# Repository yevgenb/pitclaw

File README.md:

#  Pit Claw

BBQ temperature monitor and controller built around the WT32-SC01 Plus: an
ESP32-S3 with a 3.5-inch, 480×320 landscape capacitive touchscreen. Pit Claw reads
one pit probe and two meat probes, controls a blower and optional servo damper,
and provides a web dashboard for monitoring and control. The touchscreen and
temperature control work without Wi-Fi.

## Current project state

As of **9 September 2026**:

| Area | State |
| --- | --- |
| Firmware | Version **0.2.0**, built and flashed to a WT32-SC01 Plus; upload verified and the device responded after reboot. |
| Touchscreen | LVGL Home, Graph, Settings, temperature editors, shared alarms, and first-boot setup are implemented. The latest polish is included in the flashed build. |
| Web interface | Live temperatures, history and prediction graphs, session controls/export, settings, and manual firmware OTA. Supports deployment under an Nginx path prefix. |
| Carrier PCB | **Rev B-T2F0-A5807-S4** routed prototype. Recorded KiCad ERC, DRC, schematic parity, and unconnected-item checks pass. A reviewed bare-board fabrication package is available; physical qualification remains. |
| Enclosure | **r7 landscape fit prototype**, with exported STLs, fit coupons, and a print guide. Physical module and printed-part fit still need verification. |

The firmware and simulator builds, **132 native test cases**, and the headless
LVGL checks passed on 8 September 2026. The LVGL checks include 123 navigation
taps and editor, unit, alarm, probe-state, and layout transitions. This validation
does not establish smoker temperature accuracy or qualify the new carrier's
electrical loads, thermal behavior, or physical fit.

## Touchscreen

The current dashboard uses large temperature readings, rounded cards and
navigation buttons, neutral status labels, and consistent edit icons. Smaller
degree symbols follow changing values and disappear for disconnected probes.
The image above is a native 480×320 LVGL render with example readings.

- Tap the pit card to change its setpoint, or a meat card to edit that probe's
  target. Tap for one-degree steps or hold for five-degree steps; Cancel discards
  the draft value.
- Switch between Fahrenheit and Celsius without changing the stored control
  targets. Graph history uses elapsed sample time and a dashed setpoint line.
- Alarm controls remain available on Home, Graph, Settings, and above an open
  editor. Disconnected probes display dashes.
- Setup provides Back navigation, Wi-Fi connection feedback, live probe checks,
  and separate fan, servo, and buzzer test buttons.

## Control and monitoring

- **Three probe inputs:** one pit and two meat channels, using calibrated
  thermistor probes with 2.5 mm jacks. Thermoworks Pro-Series is the intended
  probe family; other probes require suitable coefficients and calibration.
- **PID control:** fan-only, fan-and-damper, and damper-priority modes, with
  startup handling, lid-open detection, and output shutdown on a pit-probe fault.
- **Alarms:** local buzzer, browser audio, and configurable Pushover notifications.
- **Cook sessions:** temperature history, predicted meat completion times, and
  CSV/JSON export. Download a session before starting a new one.
- **Configuration:** persistent settings, probe calibration, and Wi-Fi reconnect.

## Web interface

Open `http://bbq.local` or the controller's LAN IP from a device on the same
network. The dashboard uses WebSocket updates and also works behind an Nginx
directory prefix such as `/newbbq/`; see the
[reverse-proxy guide](firmware/docs/reverse-proxy.md).

PWA installation, service-worker caching, and browser notifications need a secure
context; use HTTPS on the reverse proxy for those features. Live readings still
require a connection to the controller.

Manual firmware updates are available at `/update`. Automatic GitHub release
checks are disabled in the current PlatformIO configuration. `firmware.bin`
includes the web UI, so one firmware upload updates both interfaces while
preserving LittleFS settings and session history.

## Hardware and enclosure

The active design is the
[Rev B-T2F0-A5807-S4 carrier](hardware/carrier-revb/README.md), a 60×92 mm board
with PCB-mounted probe jacks, a blower/servo connector, a 12 V barrel inlet,
an Adafruit 5807 USB-C PD module, and a Traco TSR 2-2450N 5 V / 2 A converter.
A relay selects wall power when present and USB-PD otherwise.

| Resource | Contents |
| --- | --- |
| [Carrier design](hardware/carrier-revb/README.md) | Circuit, power limits, module mounting, and remaining qualification work |
| [Wiring guide](docs/wiring.md) | Current connector pin assignments and assembly wiring |
| [Carrier BOM](hardware/carrier-revb/bom/README.md) | Current parts and recorded pricing |
| [Verification](hardware/carrier-revb/verification/README.md) | Native electrical/layout checks and physical validation limits |
| [JLCPCB prototype package](hardware/carrier-revb/fabrication/jlcpcb-2026-09-06/README.md) | Reviewed Gerber/drill archive for a small bare-board order |
| [Fusion enclosure model](enclosure/fusion-r13/pitclaw-enclosure-r13.f3d) | Editable 104×86×44.9 mm controller case |
| [STL package and print guide](enclosure/fusion-r13/README.md) | Top, bottom, probe fascia, display retainer, USB base, coupons, and assembly guide |

The fabrication documentation records no submitted PCB order. Carrier load,
relay-transfer, thermal, and module-fit checks remain, along with printed
enclosure fit checks. Use the [enclosure guide](enclosure/README.md) for the
current controller case and the separate fan/damper assembly.

## Getting started

### 1. Set up the tools

```sh
git clone https://github.com/yevgenb/pitclaw.git
cd pitclaw
```

Install PlatformIO CLI. Windows users can use the repository's setup script:

```powershell
# Run from an elevated PowerShell in the repository root
powershell -ExecutionPolicy Bypass -File scripts\setup-dev.ps1
```

See [firmware development](docs/firmware-development.md) for prerequisites.
Use the current carrier and wiring guides when assembling hardware.

### 2. Build and flash

Run from `firmware/` with the WT32-SC01 Plus connected over USB:

```sh
cd firmware
pio run -e wt32_sc01_plus
pio run -e wt32_sc01_plus --target upload

```

No filesystem upload is needed for the web UI. A filesystem upload replaces
LittleFS and can erase configuration and session data; normal firmware updates
preserve that filesystem. The display board's programming USB port requires
opening the enclosure; the carrier's external USB-C PD port is for power.

For later manual firmware OTA, open `http://bbq.local/update` and upload
`firmware/.pio/build/wt32_sc01_plus/firmware.bin` from the repository root.

### 3. Complete setup

1. Select °F or °C in the touchscreen wizard.
2. Follow the Wi-Fi QR code and portal instructions, or continue offline with Next.
3. Connect the probes and check their live readings.
4. Tap the fan, servo, and buzzer test buttons and confirm each device operates.
5. Finish setup to enter the dashboard.

Hold a finger on the touchscreen for 10 seconds during the boot splash to request
a factory reset.

## Development and validation

The SDL2 desktop simulator runs the production LVGL screens and serves the web
UI at `http://localhost:3000`. Run these commands from `firmware/`:

```sh
# Native control-logic regression tests
pio test -e native

# Desktop simulator; requires SDL2
pio run -e simulator
.pio/build/simulator/program

# Headless production LVGL interaction checks; run after building the simulator
python3 test/ui/run_checks.py

# Web update and reverse-proxy checks
node test/web/test_release_updates.cjs
node test/web/test_reverse_proxy.cjs
```

On Apple Silicon with Homebrew SDL2, use
`CPATH=/opt/homebrew/include pio run -e simulator` if the headers are not found.
The [display test guide](firmware/test/ui/README.md) explains the capture command
and alternate SDL paths. UI screenshots can be regenerated locally on demand.

| Guide | Topics |
| --- | --- |
| [Firmware development](docs/firmware-development.md) | Build, flash, architecture, and configuration |
| [Display checks](firmware/test/ui/README.md) | Real LVGL pointer events, layout checks, and PNG capture |
| [Web UI development](docs/web-development.md) | Simulator profiles, web assets, and WebSocket protocol |
| [Reverse proxy](firmware/docs/reverse-proxy.md) | Nginx path prefixes, WebSockets, HTTPS, and manual OTA routing |
| [3D printed parts](enclosure/README.md) | Current enclosure, legacy parts, and fan assembly |

## License

TBD

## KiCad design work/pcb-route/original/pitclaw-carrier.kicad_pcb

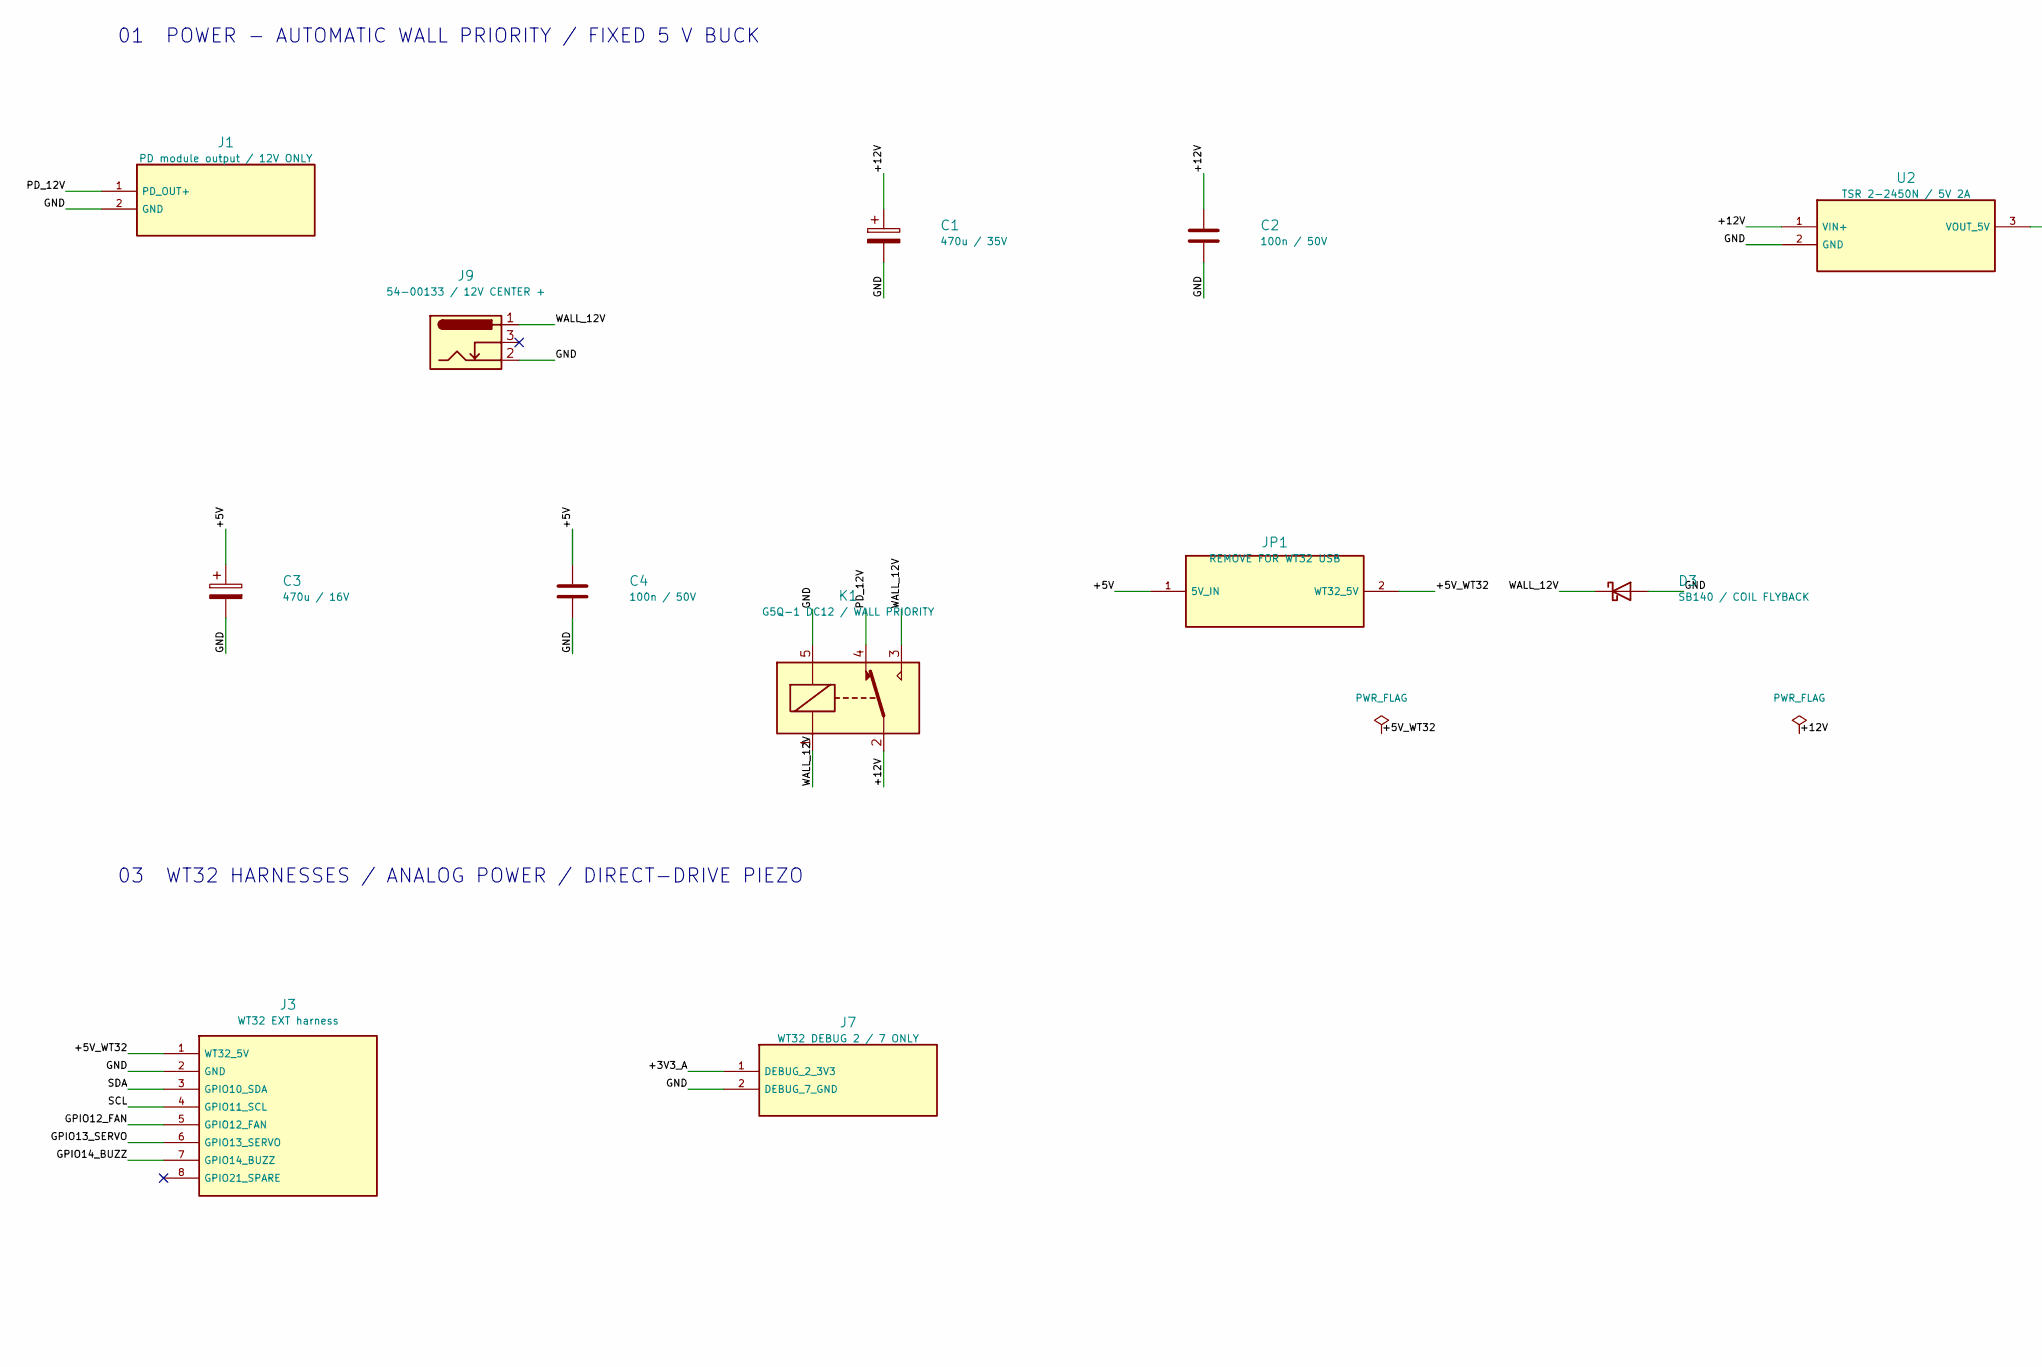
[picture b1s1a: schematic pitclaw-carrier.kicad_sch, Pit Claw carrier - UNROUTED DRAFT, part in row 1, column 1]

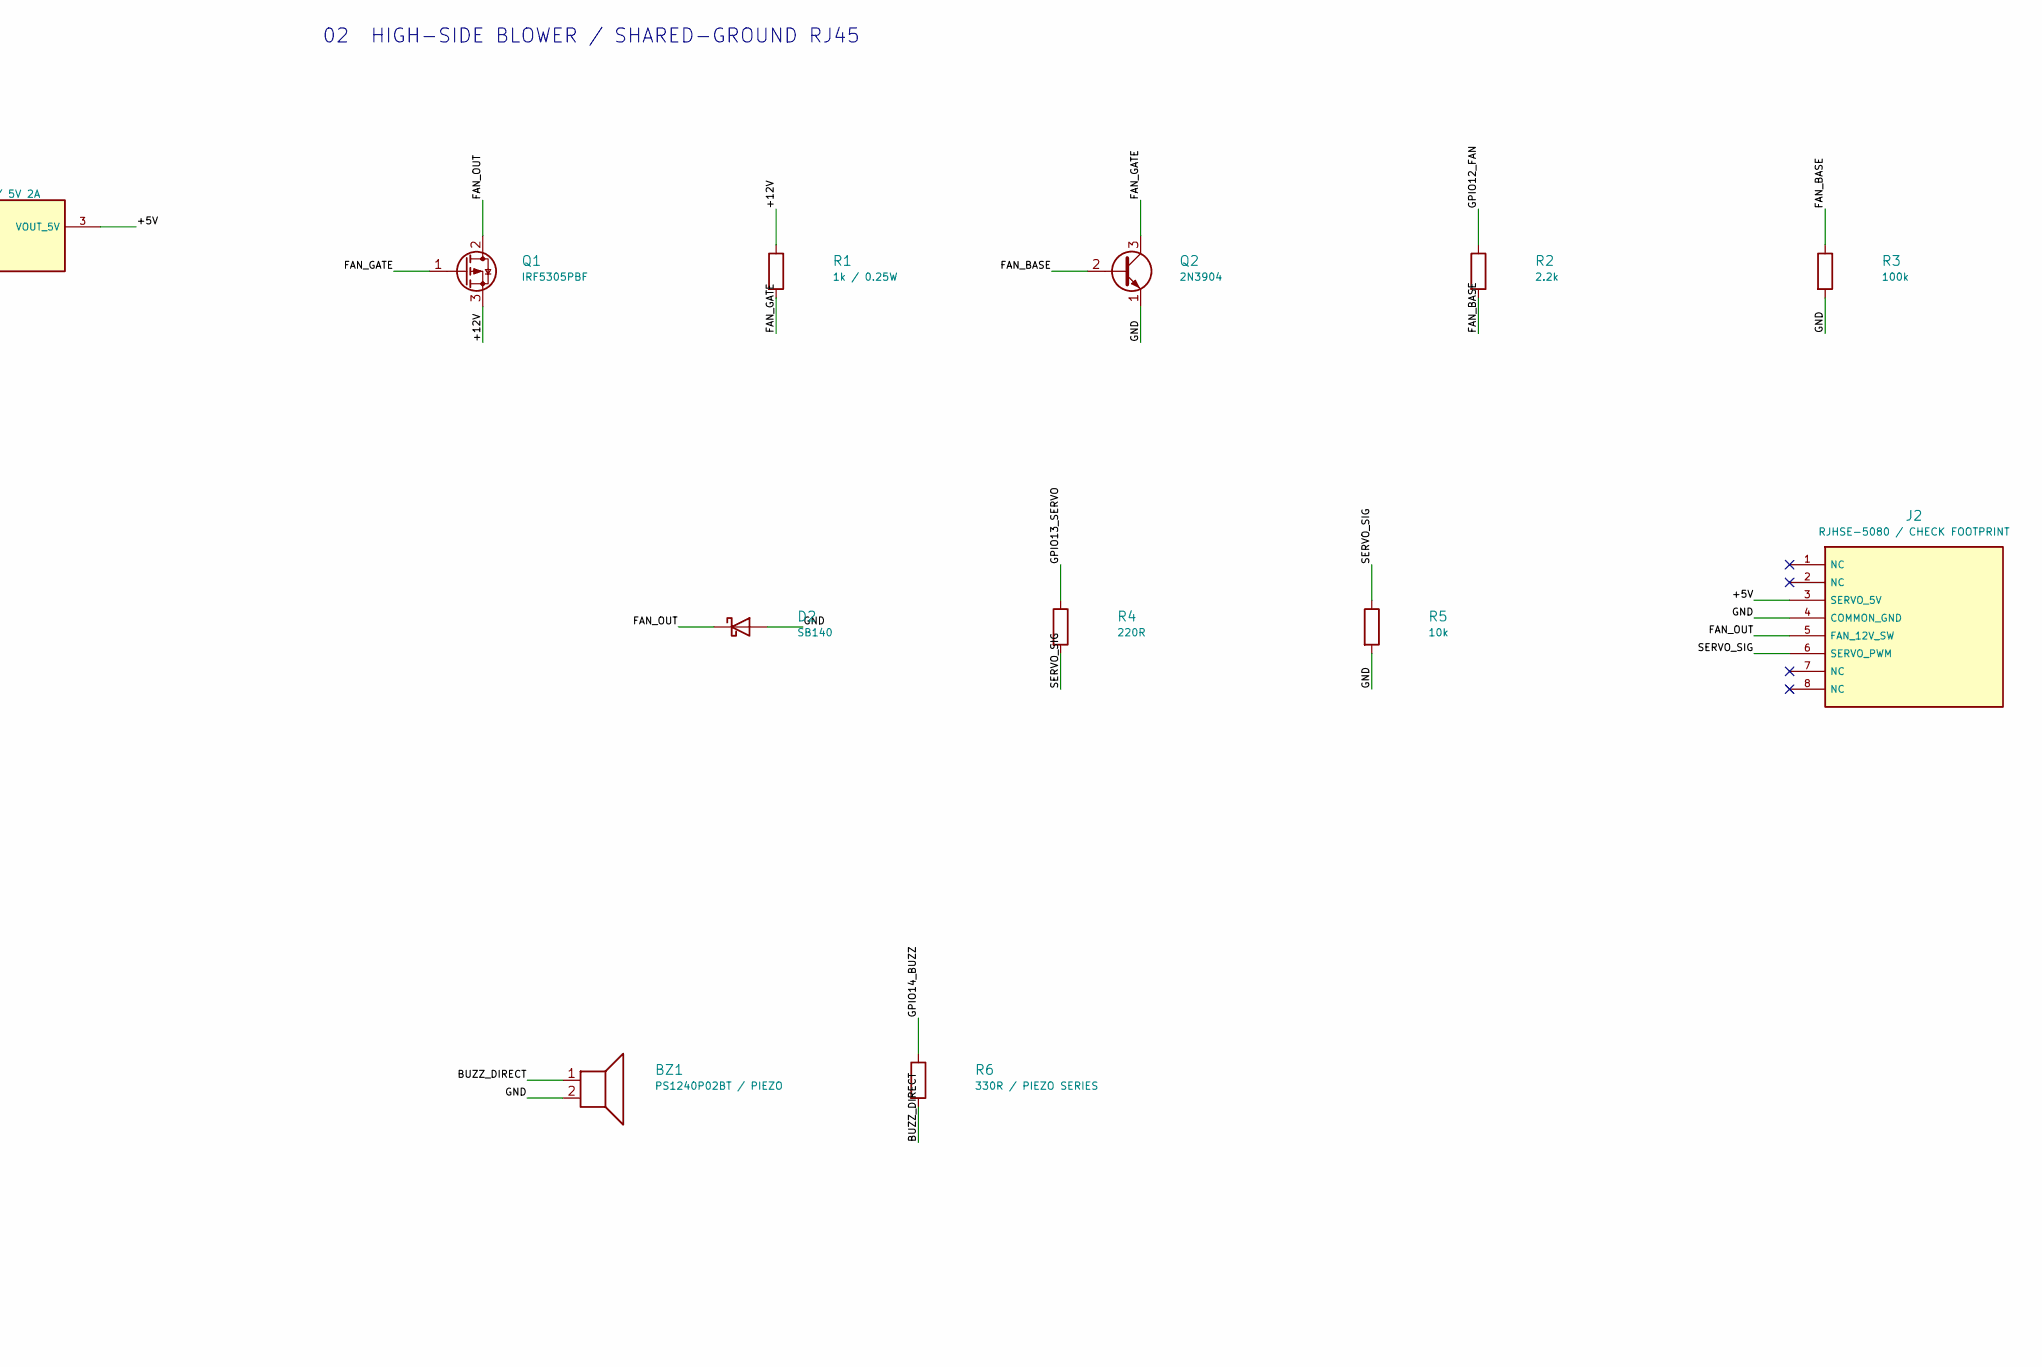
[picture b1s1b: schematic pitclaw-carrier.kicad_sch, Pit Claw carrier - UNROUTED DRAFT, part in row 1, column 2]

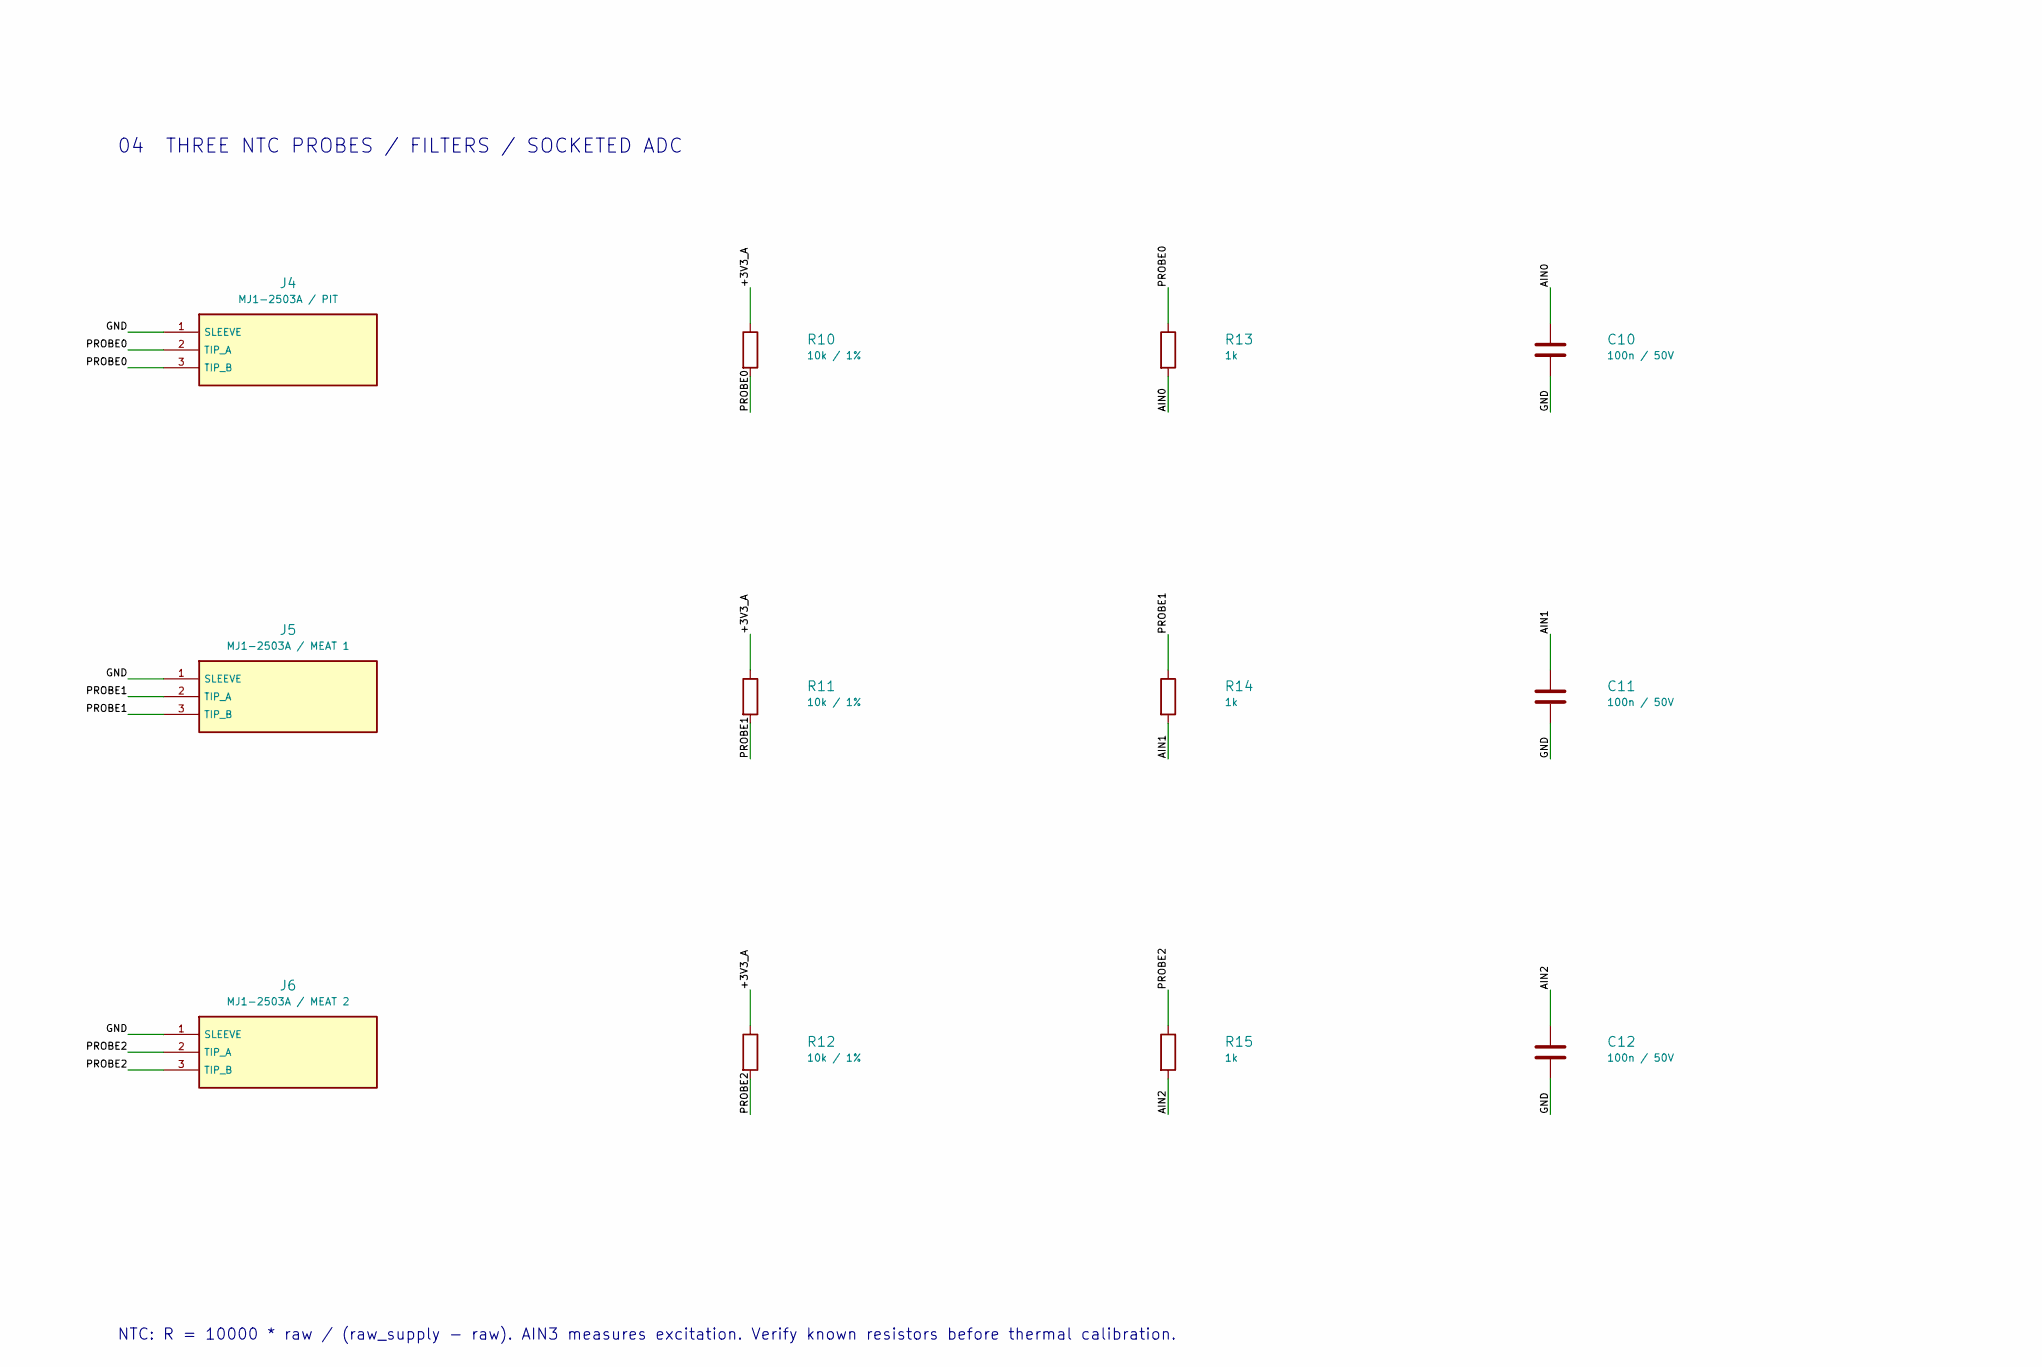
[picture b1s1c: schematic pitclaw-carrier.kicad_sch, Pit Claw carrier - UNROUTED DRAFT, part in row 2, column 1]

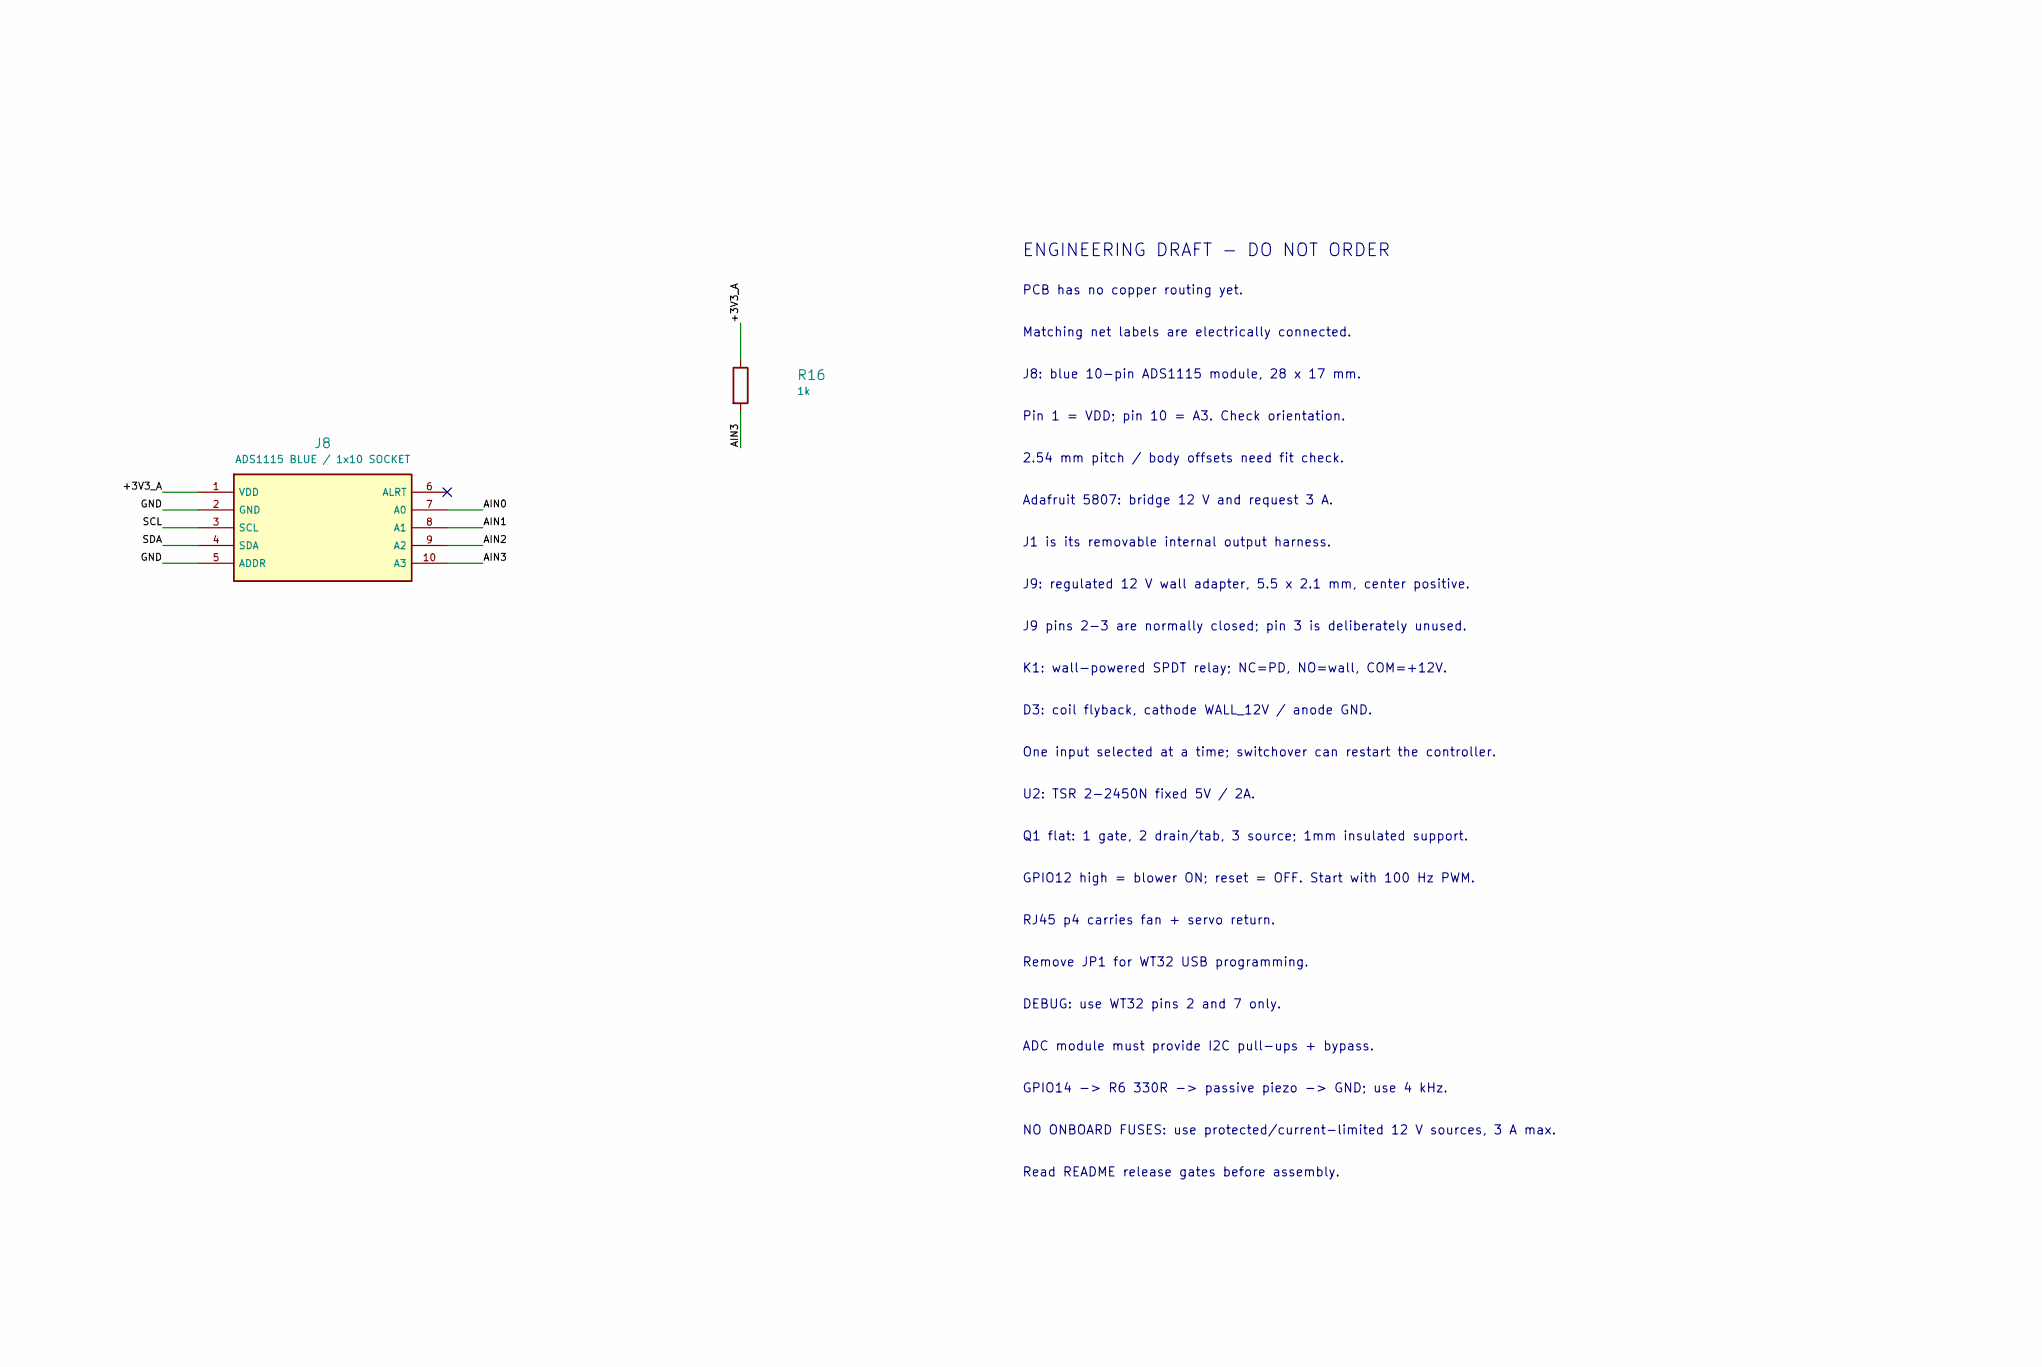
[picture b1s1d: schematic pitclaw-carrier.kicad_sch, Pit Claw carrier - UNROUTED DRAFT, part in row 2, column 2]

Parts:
BZ1: PS1240P02BT / PIEZO; Piezo_TDK_PS1240P02BT_D12.2_P5; MPN PS1240P02BT; DigiKey 445-2525-1-ND
C1: 470u / 35V; CP_Radial_D10.0mm_P5.00mm; MPN 35PX470MEFC10X12.5; DigiKey 1189-1280-ND
C2, C4, C10, C11, C12: 100n / 50V; C_TDK_FG28X7R1H104KNT06_P5; MPN FG28X7R1H104KNT06; DigiKey 445-173588-1-ND
C3: 470u / 16V; CP_Radial_D8.0mm_P3.50mm; MPN 16ZLH470MEFC8X11.5; DigiKey 1189-1859-ND
D2: SB140; D_DO-41_SOD81_P10.16mm_Horizontal; MPN SB140; DigiKey 1655-SB140CT-ND
D3: SB140 / COIL FLYBACK; D_DO-41_SOD81_P10.16mm_Horizontal; MPN SB140; DigiKey 1655-SB140CT-ND
J1: PD module output / 12V ONLY; JST_XH_B2B-XH-A_1x02_P2.50mm_Vertical; MPN B2B-XH-A; DigiKey 455-B2B-XH-A-ND
J2: RJHSE-5080 / CHECK FOOTPRINT; RJHSE-5080_DRAFT; MPN RJHSE5080; DigiKey 664-RJHSE5080-ND
J3: WT32 EXT harness; JST_XH_B8B-XH-A_1x08_P2.50mm_Vertical; MPN B8B-XH-A; DigiKey 455-B8B-XH-A-ND
J4: MJ1-2503A / PIT; MJ1-2503A; MPN MJ1-2503A; DigiKey CP1-2503AM-ND
J5: MJ1-2503A / MEAT 1; MJ1-2503A; MPN MJ1-2503A; DigiKey CP1-2503AM-ND
J6: MJ1-2503A / MEAT 2; MJ1-2503A; MPN MJ1-2503A; DigiKey CP1-2503AM-ND
J7: WT32 DEBUG 2 / 7 ONLY; JST_XH_B2B-XH-A_1x02_P2.50mm_Vertical; MPN B2B-XH-A; DigiKey 455-B2B-XH-A-ND
J8: ADS1115 BLUE / 1x10 SOCKET; ADS1115_Blue_1x10_DRAFT; MPN PPPC101LFBN-RC; DigiKey S7043-ND
J9: 54-00133 / 12V CENTER +; Tensility_54-00133_Horizontal; MPN 54-00133; DigiKey 839-54-00133-ND
JP1: REMOVE FOR WT32 USB; PinHeader_1x02_P2.54mm_Vertical; MPN 68000-102HLF; DigiKey 609-3500-ND
K1: G5Q-1 DC12 / WALL PRIORITY; Omron_G5Q1_SPDT_MaxBody; MPN G5Q-1 DC12; DigiKey Z221-ND
Q1: IRF5305PBF; IRF5305_TO220_Horizontal_TabDown; MPN IRF5305PBF; DigiKey IRF5305PBF-ND
Q2: 2N3904; TO-92_Inline_Wide; MPN 2N3904BU; DigiKey 2N3904FS-ND
R1: 1k / 0.25W; R_Axial_DIN0207_L6.3mm_D2.5mm_P7.62mm_Horizontal; MPN MFR-25FBF52-1K; DigiKey 1.00KXBK-ND
R2: 2.2k; R_Axial_DIN0207_L6.3mm_D2.5mm_P7.62mm_Horizontal; MPN MFR-25FBF52-2K2; DigiKey MFR-25FBF52-2K2-ND
R3: 100k; R_Axial_DIN0207_L6.3mm_D2.5mm_P7.62mm_Horizontal; MPN MFR-25FBF52-100K; DigiKey 100KXBK-ND
R4: 220R; R_Axial_DIN0207_L6.3mm_D2.5mm_P7.62mm_Horizontal; MPN MFR-25FBF52-220R; DigiKey MFR-25FBF52-220R-ND
R5: 10k; R_Axial_DIN0207_L6.3mm_D2.5mm_P7.62mm_Horizontal; MPN MFR-25FBF52-10K; DigiKey 10.0KXBK-ND
R6: 330R / PIEZO SERIES; R_Axial_DIN0207_L6.3mm_D2.5mm_P7.62mm_Horizontal; MPN MFR-25FBF52-330R; DigiKey MFR-25FBF52-330R-ND
R10, R11, R12: 10k / 1%; R_Axial_DIN0207_L6.3mm_D2.5mm_P7.62mm_Horizontal; MPN MFR-25FBF52-10K; DigiKey 10.0KXBK-ND
R13, R14, R15, R16: 1k; R_Axial_DIN0207_L6.3mm_D2.5mm_P7.62mm_Horizontal; MPN MFR-25FBF52-1K; DigiKey 1.00KXBK-ND
U2: TSR 2-2450N / 5V 2A; TRACO_TSR_2N_SIP3; MPN TSR 2-2450N; DigiKey 1951-TSR2-2450N-ND

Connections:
/+3V3_A: J7.1 (DEBUG_2_3V3), J8.1 (VDD), R10.1, R11.1, R12.1, R16.1
/+5V: C3.1, C4.1, J2.3 (SERVO_5V), JP1.1 (5V_IN), U2.3 (VOUT_5V)
/+5V_WT32: J3.1 (WT32_5V), JP1.2 (WT32_5V)
/+12V: C1.1, C2.1, K1.2, Q1.3 (S), R1.1, U2.1 (VIN+)
/AIN0: C10.1, J8.7 (A0), R13.2
/AIN1: C11.1, J8.8 (A1), R14.2
/AIN2: C12.1, J8.9 (A2), R15.2
/AIN3: J8.10 (A3), R16.2
/BUZZ_DIRECT: BZ1.1, R6.2
/FAN_BASE: Q2.2 (B), R2.2, R3.1
/FAN_GATE: Q1.1 (G), Q2.3 (C), R1.2
/FAN_OUT: D2.1 (K), J2.5 (FAN_12V_SW), Q1.2 (D)
/GND: BZ1.2, C1.2, C2.2, C3.2, C4.2, C10.2, C11.2, C12.2, D2.2 (A), D3.2 (A), J1.2 (GND), J2.4 (COMMON_GND), J3.2 (GND), J4.1 (SLEEVE), J5.1 (SLEEVE), J6.1 (SLEEVE), J7.2 (DEBUG_7_GND), J8.2 (GND), J8.5 (ADDR), J9.2, K1.5, Q2.1 (E), R3.2, R5.2, U2.2 (GND)
/GPIO12_FAN: J3.5 (GPIO12_FAN), R2.1
/GPIO13_SERVO: J3.6 (GPIO13_SERVO), R4.1
/GPIO14_BUZZ: J3.7 (GPIO14_BUZZ), R6.1
/PD_12V: J1.1 (PD_OUT+), K1.4
/PROBE0: J4.2 (TIP_A), J4.3 (TIP_B), R10.2, R13.1
/PROBE1: J5.2 (TIP_A), J5.3 (TIP_B), R11.2, R14.1
/PROBE2: J6.2 (TIP_A), J6.3 (TIP_B), R12.2, R15.1
/SCL: J3.4 (GPIO11_SCL), J8.3 (SCL)
/SDA: J3.3 (GPIO10_SDA), J8.4 (SDA)
/SERVO_SIG: J2.6 (SERVO_PWM), R4.2, R5.1
/WALL_12V: D3.1 (K), J9.1, K1.1, K1.3

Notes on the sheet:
01 POWER - AUTOMATIC WALL PRIORITY / FIXED 5 V BUCK
02 HIGH-SIDE BLOWER / SHARED-GROUND RJ45
03 WT32 HARNESSES / ANALOG POWER / DIRECT-DRIVE PIEZO
04 THREE NTC PROBES / FILTERS / SOCKETED ADC
ENGINEERING DRAFT - DO NOT ORDER
PCB has no copper routing yet.
Matching net labels are electrically connected.
J8: blue 10-pin ADS1115 module, 28 x 17 mm.
Pin 1 = VDD; pin 10 = A3. Check orientation.
2.54 mm pitch / body offsets need fit check.
Adafruit 5807: bridge 12 V and request 3 A.
J1 is its removable internal output harness.
J9: regulated 12 V wall adapter, 5.5 x 2.1 mm, center positive.
J9 pins 2-3 are normally closed; pin 3 is deliberately unused.
K1: wall-powered SPDT relay; NC=PD, NO=wall, COM=+12V.
D3: coil flyback, cathode WALL_12V / anode GND.
One input selected at a time; switchover can restart the controller.
U2: TSR 2-2450N fixed 5V / 2A.
Q1 flat: 1 gate, 2 drain/tab, 3 source; 1mm insulated support.
GPIO12 high = blower ON; reset = OFF. Start with 100 Hz PWM.
RJ45 p4 carries fan + servo return.
Remove JP1 for WT32 USB programming.
DEBUG: use WT32 pins 2 and 7 only.
ADC module must provide I2C pull-ups + bypass.
GPIO14 -> R6 330R -> passive piezo -> GND; use 4 kHz.
NO ONBOARD FUSES: use protected/current-limited 12 V sources, 3 A max.
Read README release gates before assembly.
NTC: R = 10000 * raw / (raw_supply - raw). AIN3 measures excitation. Verify known resistors before thermal calibration.

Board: 2 copper layers, 43 parts (0 on the bottom side), 24 nets, no tracks yet.

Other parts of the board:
H1, H2, H3, H4: Mount_M3_D3.2_CLEARANCE
H5, H6: ADAFRUIT 5807 M2 / 2.4 NPTH; Adafruit5807_M2_Mount

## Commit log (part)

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2026-04-16 ci: bump softprops/action-gh-release from 2 to 3
    Bumps [softprops/action-gh-release](https://github.com/softprops/action-gh-release) from 2 to 3.
    - [Release notes](https://github.com/softprops/action-gh-release/releases)
    - [Changelog](https://github.com/softprops/action-gh-release/blob/master/CHANGELOG.md)
    - [Commits](https://github.com/softprops/action-gh-release/compare/v2...v3)
    ---
    updated-dependencies:
2026-06-18 ci: bump actions/checkout from 6 to 7
    Bumps [actions/checkout](https://github.com/actions/checkout) from 6 to 7.
    - [Release notes](https://github.com/actions/checkout/releases)
    - [Changelog](https://github.com/actions/checkout/blob/main/CHANGELOG.md)
    - [Commits](https://github.com/actions/checkout/compare/v6...v7)
    ---
    updated-dependencies:
2026-06-25 ci: bump actions/cache from 5 to 6
    Bumps [actions/cache](https://github.com/actions/cache) from 5 to 6.
    - [Release notes](https://github.com/actions/cache/releases)
    - [Changelog](https://github.com/actions/cache/blob/main/RELEASES.md)
    - [Commits](https://github.com/actions/cache/compare/v5...v6)
    ---
    updated-dependencies:
